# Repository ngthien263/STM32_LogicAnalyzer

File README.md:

# STM32_LogicAnalyzer
## Project Overview
This project involves creating a logic analyzer using the STM32F103 microcontroller. The analyzer reads input data, handles PWM signals, and displays the captured data on a GUI.

## Features
- Real-time data capture from multiple channels
- PWM signal handling
- GUI for data visualization
  
## Pin Configuration
  - Timer:     
    - **PA0**: TIM2_CH1 (Input Capture)
    - **PA1**: TIM2_CH2 (Input Capture)
    - **PA2**: TIM2_CH3 (Input Capture)
    - **PA3**: TIM2_CH4 (Input Capture)
  - ADC:
    - **PA4**: ADC1_IN4
    - **PA5**: ADC1_IN5
  - Communication:
    - **PA9**: USART1_TX (UART Communication)
    - **PA10**: USART1_RX (UART Communication)
    - **PA11**: USB_DM (USB Communication)
    - **PA12**: USB_DP (USB Communication)

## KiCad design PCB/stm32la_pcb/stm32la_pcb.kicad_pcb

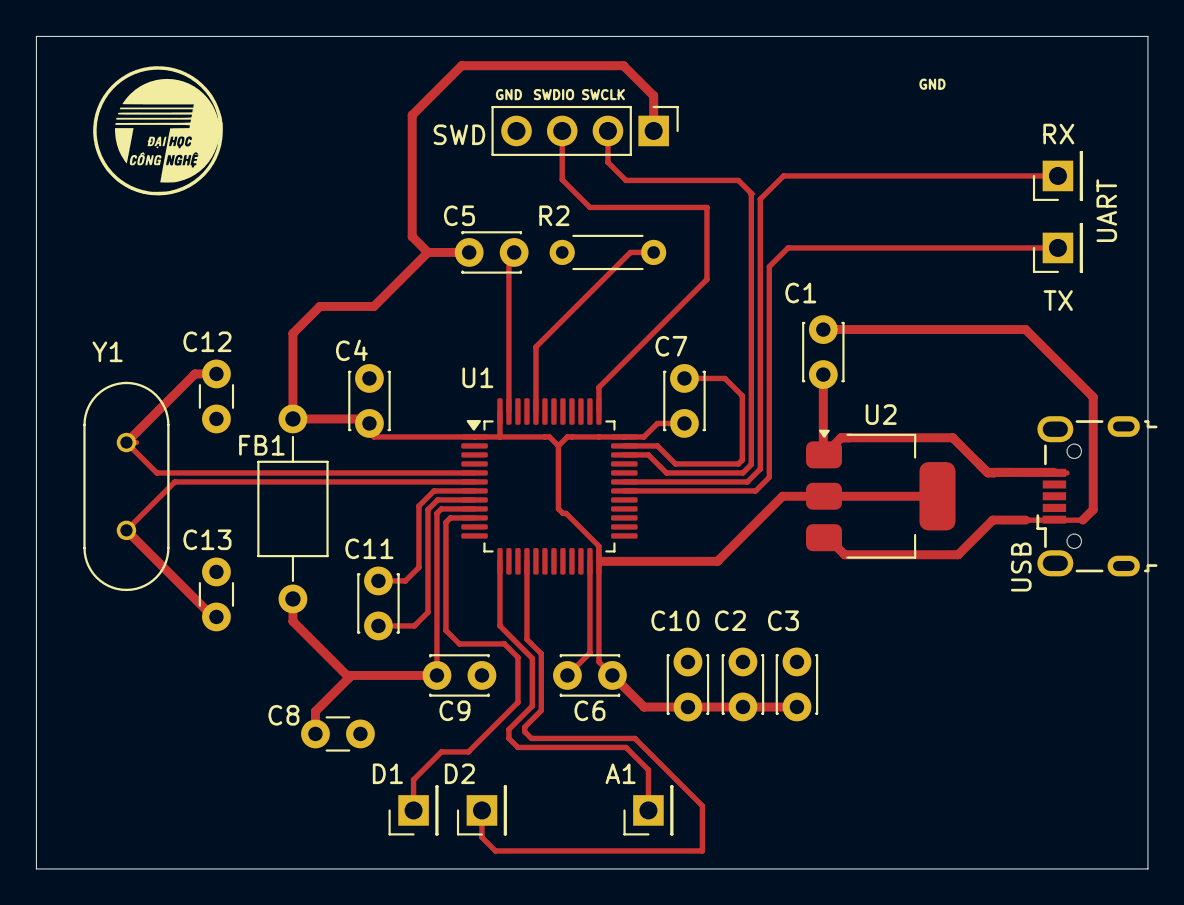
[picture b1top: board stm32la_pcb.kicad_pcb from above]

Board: 2 copper layers, 61.8 x 46.2 mm, 25 parts (0 on the bottom side), 15 nets.

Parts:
A1: Conn_01x01_Pin; PinHeader_1x01_P2.54mm_Vertical
C1, C2: 22u; C_Disc_D3.0mm_W2.0mm_P2.50mm
C3: 10u; C_Disc_D3.0mm_W2.0mm_P2.50mm
C4, C5, C6, C7, C11: 100n; C_Disc_D3.0mm_W2.0mm_P2.50mm
C8: 10n; C_Disc_D3.0mm_W1.6mm_P2.50mm
C9, C10: 1u; C_Disc_D3.0mm_W2.0mm_P2.50mm
C12, C13: 10p; C_Disc_D3.0mm_W1.6mm_P2.50mm
D1, D2: Conn_01x01_Pin; PinHeader_1x01_P2.54mm_Vertical
FB1: 120R; L_Axial_L5.0mm_D3.6mm_P10.00mm_Horizontal_Murata_BL01RN1A2A2
R2: 10k; R_Axial_DIN0204_L3.6mm_D1.6mm_P5.08mm_Horizontal
RX: Conn_01x01_Pin; PinHeader_1x01_P2.54mm_Vertical
SWD: Conn_01x04_Pin; PinHeader_1x04_P2.54mm_Vertical
TX: Conn_01x01_Pin; PinHeader_1x01_P2.54mm_Vertical
U1: STM32F103C8Tx; LQFP-48_7x7mm_P0.5mm
U2: AMS1117-3.3; SOT-223-3_TabPin2
USB: USB_B_Micro; USB_Micro-B_Wuerth_629105150521
Y1: Crystal; XTAL_HC49P488W43L1150T466H350

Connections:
+3.3V: C2.1, C3.1, C4.1, C5.1, C6.1, C7.1, C10.1, FB1.1, SWD.1, U1.1 (VBAT), U1.24 (VDD), U1.36 (VDD), U1.48 (VDD), U2.2 (VO)
+3.3VA: C8.1, C9.1, FB1.2, U1.9 (VDDA)
/A_IN: A1.1, U1.13 (PA3)
/BOOT0: R2.1, U1.44 (BOOT0)
/CH1: D1.1, U1.10 (PA0)
/CH2: D2.1, U1.16 (PA6)
/HSE_IN: C12.1, U1.5 (PD0), Y1.1
/HSE_OUT: C13.1, U1.6 (PD1), Y1.2
/NRST: C11.1, U1.7 (NRST)
/SWCLK: SWD.2, U1.34 (PA13)
/SWDIO: SWD.3, U1.37 (PA14)
/USART1_RX: RX.1, U1.31 (PA10)
/USART1_TX: TX.1, U1.30 (PA9)
GND: C1.2, C2.2, C3.2, C4.2, C5.2, C6.2, C7.2, C8.2, C9.2, C10.2, C11.2, C12.2, C13.2, R2.2, SWD.4, U1.8 (VSSA), U1.23 (VSS), U1.35 (VSS), U1.47 (VSS), U2.1 (GND), USB.5 (GND)
VBUS: C1.1, U2.3 (VI), USB.1 (VBUS)

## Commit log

2024-09-23 remove files
2024-09-23 gitattributes
2024-09-26 RCC driver
2024-09-26 Fix calculation errors
2024-09-26 new branch
2024-10-01 Timer2 PWM Input Configure
2024-10-01 Thien (#8)
    * update
    * Timer2 PWM Input Configure
    * Update README.md
2024-10-02 Timer Driver
2024-10-08 change TIM_Init function, adding pwm function
2024-10-08 update main
2024-10-09 Update oc pwm function
2024-10-15 UART driver
2024-10-15 Enable CC2 Interrupt
2024-10-22 UART Init, sending data
2024-10-22 fixing OC incorrect output frequency
2024-10-30 ver 1
2024-12-04 fix crash
2024-12-04 update plot
2024-12-06 update plotting
2024-12-06 update ch2 pwmic
2024-12-08 test ver
2024-12-30 rm file
2024-12-30 update sw
